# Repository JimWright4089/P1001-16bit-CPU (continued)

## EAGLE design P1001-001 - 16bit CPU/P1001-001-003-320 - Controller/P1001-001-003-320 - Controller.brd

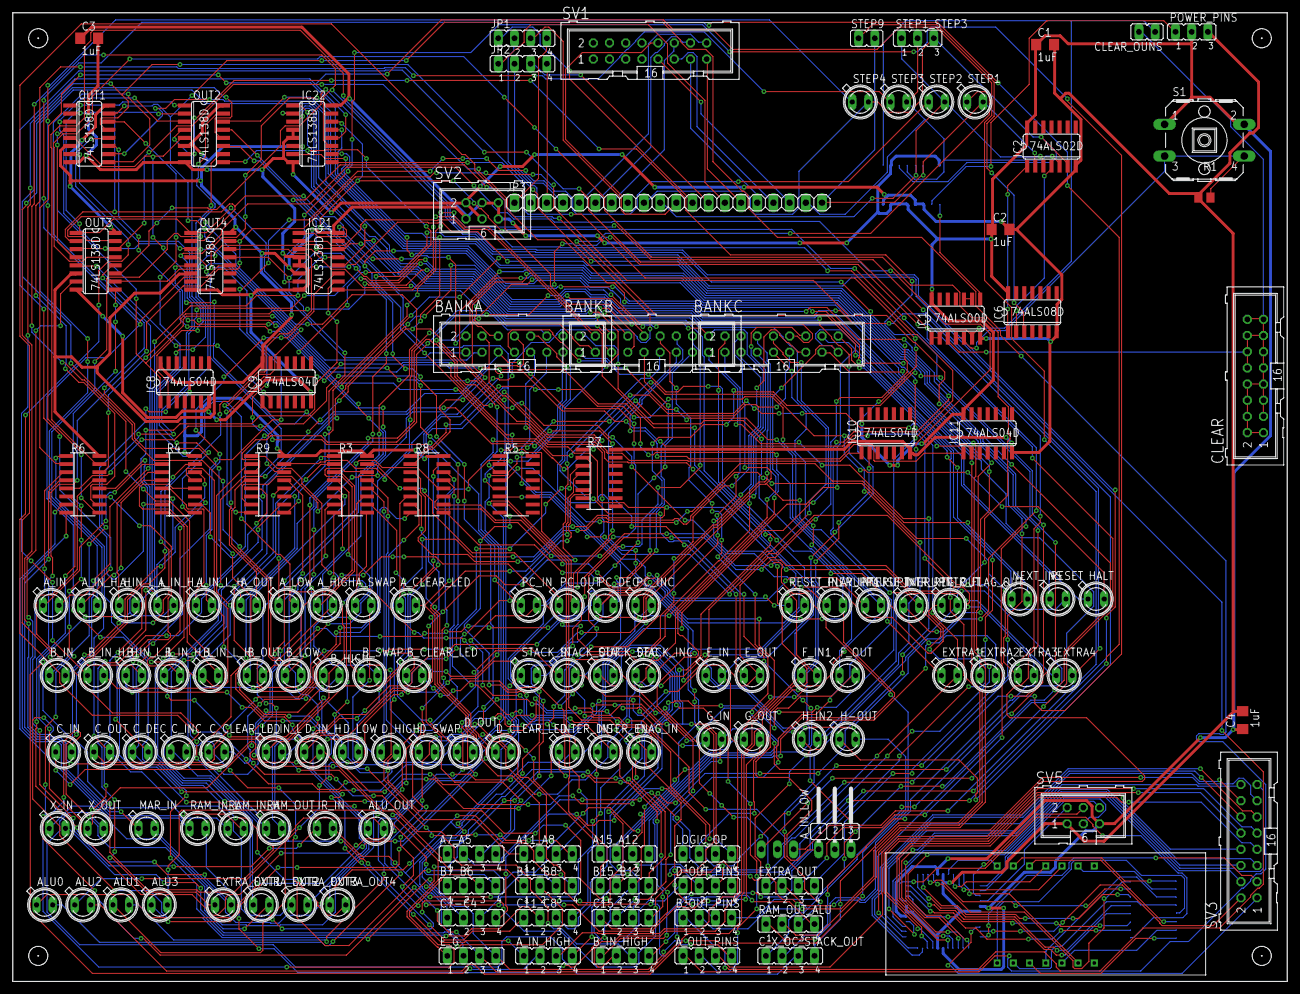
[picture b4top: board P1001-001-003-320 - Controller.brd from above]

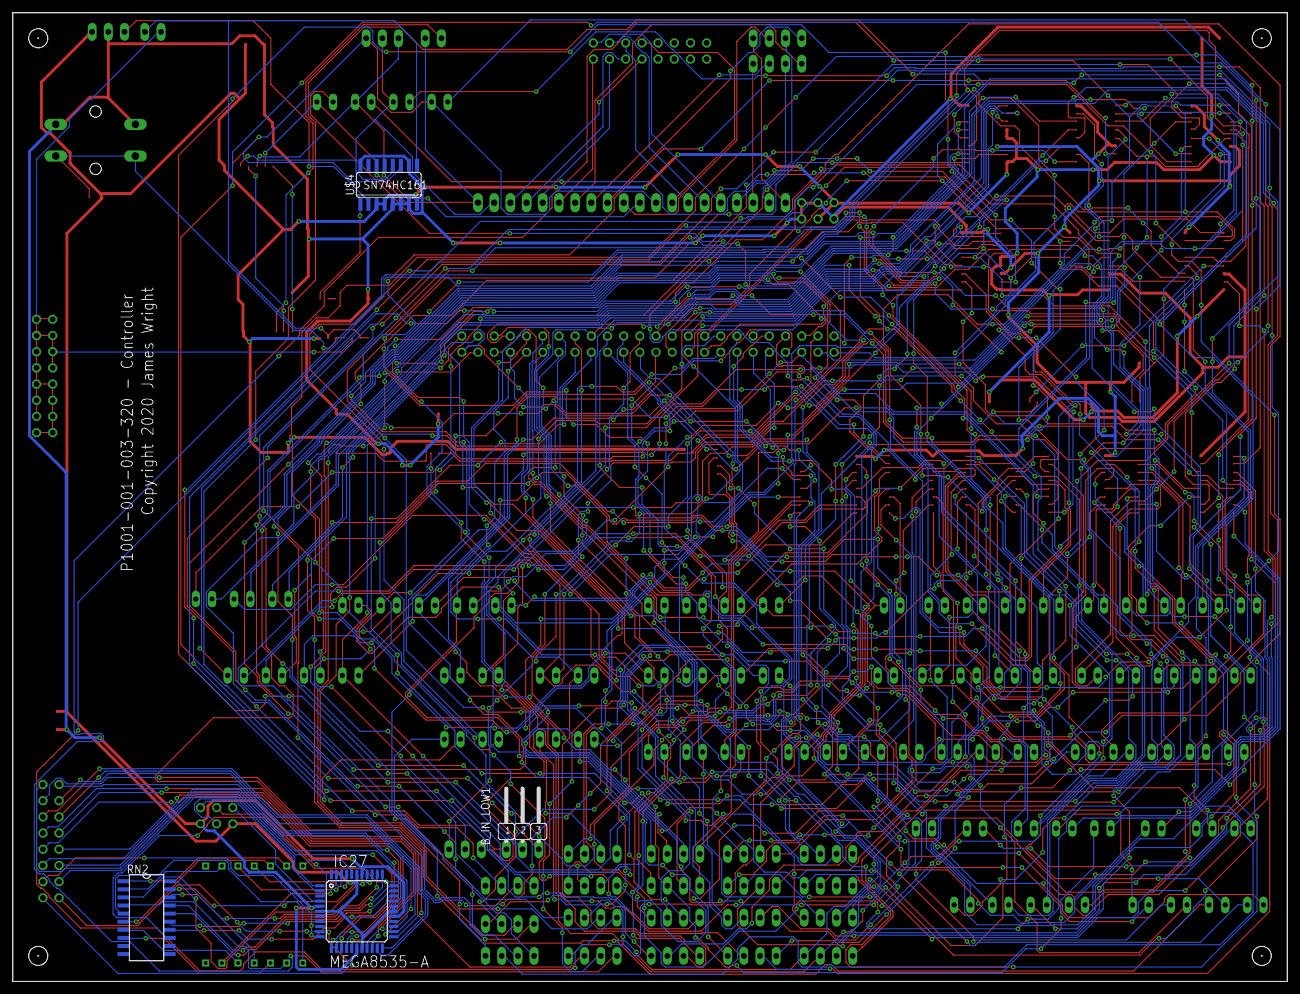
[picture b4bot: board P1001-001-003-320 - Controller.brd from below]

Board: 2 copper layers, 200.0 x 152.0 mm, 149 parts (4 on the bottom side), 248 nets.

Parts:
A7_A5, A11_A8, A15_A12: JP4
ALU0, ALU1, ALU2, ALU3: SFH482
ALU_OUT: SFH482
A_CLEAR_LED: SFH482
A_HIGH: SFH482
A_IN: SFH482
A_IN_HIGH: JP4
A_IN_H_H: SFH482
A_IN_H_L: SFH482
A_IN_LOW: JP2W
A_IN_L_H: SFH482
A_IN_L_L: SFH482
A_LOW: SFH482
A_OUT: SFH482
A_OUT_PINS: JP4
A_SWAP: SFH482
B7_B6, B11_B8, B15_B12: JP4
BANKA: ML16
BANKB: ML16
BANKC: ML16
B_CLEAR_LED: SFH482
B_HIGH: SFH482
B_IN: SFH482
B_IN_HIGH: JP4
B_IN_H_H: SFH482
B_IN_H_L: SFH482
B_IN_LOW1: JP2W
B_IN_L_H: SFH482
B_IN_L_L: SFH482
B_LOW: SFH482
B_OUT: SFH482
B_OUT_PINS: JP4
B_SWAP: SFH482
C1, C2, C3, C4: 1uF; C1206
C7-C4, C11_C8, C15_C12: JP4
CLEAR: ML16
CLEAR_OUNS: JP1
C_CLEAR_LED: SFH482
C_DEC: SFH482
C_IN: SFH482
C_INC: SFH482
C_OUT: SFH482
C_X_OC_STACK_OUT: JP4
D_CLEAR_LED: SFH482
D_HIGH: SFH482
D_IN_H: SFH482
D_IN_L: SFH482
D_LOW: SFH482
D_OUT: SFH482
D_OUT_PINS: JP4
D_SWAP: SFH482
EXTRA1, EXTRA2, EXTRA3, EXTRA4: SFH482
EXTRA_OUT: JP4
EXTRA_OUT1, EXTRA_OUT2, EXTRA_OUT3, EXTRA_OUT4: SFH482
E_G: JP4
E_IN: SFH482
E_OUT: SFH482
FLAG_IN: SFH482
F_IN1: SFH482
F_OUT: SFH482
G_IN: SFH482
G_OUT: SFH482
H-OUT: SFH482
HALT: SFH482
H_IN2: SFH482
IC1: 74ALS00D; SO14
IC2: 74ALS02D; SO14
IC6: 74ALS08D; SO14
IC8, IC9, IC10, IC11: 74ALS04D; SO14
IC21, IC22: 74LS138D; SO16
IC27: MEGA8535-A; TQFP44
INTER_DIS: SFH482
INTER_EN: SFH482
INTR_FLAG_OUT: SFH482
INTR_REG_OUT: SFH482
IR_IN: SFH482
JP1, JP2: JP4
JP3: 1X20
LOGIC_OP: JP4
MAR_IN: SFH482
NEXT_INS: SFH482
OUT1, OUT2, OUT3, OUT4: 74LS138D; SO16
PAUSE_INERUPT: SFH482
PC_DEC: SFH482
PC_IN: SFH482
PC_INC: SFH482
PC_OUT: SFH482
PLAY_INTERUPT: SFH482
POWER_PINS: JP2
R1: M0805
R3, R4, R5, R6, R7, R8, R9: SO16
RAM_IN_H: SFH482
RAM_IN_L: SFH482
RAM_OUT: SFH482
RAM_OUT_ALU: JP4
RESET: SFH482
RESET_INERUPT1: SFH482
RN2: SOMC20
S1: B3F-40XX
STACK_DEC: SFH482
STACK_IN: SFH482
STACK_INC: SFH482
STACK_OUT: SFH482
STEP1, STEP2, STEP3, STEP4: SFH482
STEP1_STEP3: JP2
STEP9: JP1
SV1, SV3: ML16
SV2, SV5: ML6
U$1: 4-DIGIT-7-SEGMENT
U$4: SN74HC161; SO16
X_IN: SFH482
X_OUT: SFH482

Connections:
!CLEAR: CLEAR_OUNS.1, IC1.1, IC1.2, IC1.6, U$4.9
A: IC27.37, RN2.20
B: IC27.36, RN2.19
C: IC27.35, RN2.18
CLEAR: CLEAR.1, CLEAR.2, CLEAR.3, CLEAR.4, CLEAR.5, CLEAR.6, CLEAR.7, CLEAR.8, CLEAR.9, CLEAR.10, CLEAR.11, CLEAR.12, CLEAR.13, CLEAR.14, CLEAR.15, CLEAR.16, CLEAR_OUNS.2, IC1.3
CLK: POWER_PINS.1, U$4.2
D: IC27.34, RN2.17
DATAA0: BANKA.1, OUT1.1, OUT2.1, OUT3.1, OUT4.1
DATAA1: BANKA.2, OUT1.2, OUT2.2, OUT3.2, OUT4.2
DATAA2: BANKA.3, OUT1.3, OUT2.3, OUT3.3, OUT4.3
DATAA3: BANKA.4, IC8.1, IC10.1, OUT1.4, OUT3.4
DATAA4: BANKA.5, IC9.1, IC11.1, OUT1.5, OUT2.5
DATAA5: A7_A5.2, BANKA.6, EXTRA1.K
DATAA6: A7_A5.3, BANKA.7, EXTRA2.K
DATAA7: A7_A5.4, BANKA.8, EXTRA3.K
DATAA8: A11_A8.1, BANKA.9, EXTRA4.A
DATAA9: A11_A8.2, A_CLEAR_LED.K, BANKA.10
DATAA10: A11_A8.3, BANKA.11, B_CLEAR_LED.K
DATAA11: A11_A8.4, BANKA.12, C_CLEAR_LED.K
DATAA12: A15_A12.1, BANKA.13, D_CLEAR_LED.K
DATAA13: A15_A12.2, BANKA.14, RESET_INERUPT1.K
DATAA14: A15_A12.3, BANKA.15, PAUSE_INERUPT.K
DATAA15: A15_A12.4, BANKA.16, PLAY_INTERUPT.K
DATAB0: BANKB.1, IC21.1
DATAB1: BANKB.2, IC21.2
DATAB2: BANKB.3, IC21.3
DATAB3: BANKB.4, IC22.1
DATAB4: BANKB.5, IC22.2
DATAB5: BANKB.6, IC22.3
DATAB6: B7_B6.3, BANKB.7, C_IN.K
DATAB7: B7_B6.4, BANKB.8, D_IN_L.K
DATAB8: B11_B8.1, BANKB.9, D_IN_H.K
DATAB9: B11_B8.2, BANKB.10, X_IN.K
DATAB10: B11_B8.3, BANKB.11, IR_IN.K
DATAB11: B11_B8.4, BANKB.12, MAR_IN.K
DATAB12: B15_B12.1, BANKB.13, PC_IN.K
DATAB13: B15_B12.2, BANKB.14, STACK_IN.K
DATAB14: B15_B12.3, BANKB.15, RAM_IN_L.K
DATAB15: B15_B12.4, BANKB.16, RAM_IN_H.K
DATAC0: ALU0.K, BANKC.1, LOGIC_OP.4
DATAC1: ALU1.K, BANKC.2, LOGIC_OP.3
DATAC2: ALU2.K, BANKC.3, LOGIC_OP.2
DATAC3: ALU3.K, BANKC.4, LOGIC_OP.1
DATAC4: BANKC.5, C7-C4.1, PC_DEC.A
DATAC5: BANKC.6, C7-C4.2, PC_INC.A
DATAC6: BANKC.7, C7-C4.3, STACK_INC.A
DATAC7: BANKC.8, C7-C4.4, STACK_DEC.A
DATAC8: BANKC.9, C11_C8.1, C_INC.A
DATAC9: BANKC.10, C11_C8.2, C_DEC.A
DATAC10: BANKC.11, C11_C8.3, FLAG_IN.A
DATAC11: BANKC.12, C11_C8.4, INTER_EN.A
DATAC12: BANKC.13, C15_C12.1, INTER_DIS.A
DATAC13: BANKC.14, C15_C12.2, RESET.A
DATAC14: BANKC.15, C15_C12.3, HALT.A
DATAC15: BANKC.16, C15_C12.4, NEXT_INS.A
DIG0: IC27.40, U$1.PIN14
DIG1: IC27.41, U$1.PIN11
DIG2: IC27.42, U$1.PIN10
DIG3: IC27.43, U$1.PIN6
DP: IC27.30, RN2.13
E: IC27.33, RN2.16
EXTERN_BUS0: IC27.9, SV3.1
EXTERN_BUS1: IC27.10, SV3.2
EXTERN_BUS2: IC27.11, SV3.3
EXTERN_BUS3: IC27.12, SV3.4
EXTERN_BUS4: IC27.13, SV3.5
EXTERN_BUS5: IC27.14, SV3.6
EXTERN_BUS6: IC27.15, SV3.7
EXTERN_BUS7: IC27.16, SV3.8
EXTERN_BUS8: IC27.19, SV3.9
EXTERN_BUS9: IC27.20, SV3.10
EXTERN_BUS10: IC27.21, SV3.11
EXTERN_BUS11: IC27.22, SV3.12
EXTERN_BUS12: IC27.23, SV3.13
EXTERN_BUS13: IC27.24, SV3.14
EXTERN_BUS14: IC27.25, SV3.15
EXTERN_BUS15: IC27.26, SV3.16
F: IC27.32, RN2.15
FIRST_STEP: IC6.3, STEP9.1
G: IC27.31, RN2.14
GND: C1.2, C2.2, C3.2, C4.2, IC1.7, IC2.7, IC6.7, IC8.7, IC9.7, IC10.7, IC11.7, IC21.4, IC21.5, IC21.8, IC22.4, IC22.5, IC22.8, IC27.6, IC27.18, IC27.28, IC27.29, IC27.39, OUT1.8, OUT2.8, OUT3.8, OUT4.8, POWER_PINS.3, R1.1, R7.16, SV2.2, SV2.3, SV5.1, U$4.3, U$4.4, U$4.8
IN_BUS0: IC2.2, JP3.20, STEP1.K, STEP9.2, U$4.14
IN_BUS1: IC2.3, JP3.10, STEP1_STEP3.1, STEP2.K, U$4.13
IN_BUS2: IC2.5, JP3.19, STEP1_STEP3.2, STEP3.K, U$4.12
IN_BUS3: IC2.6, JP3.9, STEP1_STEP3.3, STEP4.K, U$4.11
IN_BUS4: JP3.18, SV1.9
IN_BUS5: JP3.8, SV1.10
IN_BUS6: JP3.17, SV1.11
IN_BUS7: JP3.7, SV1.12
IN_BUS8: JP3.16, SV1.13
IN_BUS9: JP3.6, SV1.14
IN_BUS10: JP3.15, SV1.15
IN_BUS11: JP3.5, SV1.16
IN_BUS12: JP2.1, JP3.14
IN_BUS13: JP2.2, JP3.4
IN_BUS14: JP2.3, JP3.13
IN_BUS15: JP2.4, JP3.3
IN_BUS16: JP1.1, JP3.12
IN_BUS17: JP1.2, JP3.2
IN_BUS18: JP1.3, JP3.11
IN_BUS19: JP1.4, JP3.1
unnamed: IC1.4, IC1.5, R1.2, S1.3, S1.4
unnamed: EXTRA1.A, R8.1
unnamed: EXTRA2.A, R8.2
unnamed: R8.13, X_IN.A
unnamed: EXTRA4.K, R5.3
unnamed: EXTRA3.A, R8.3
unnamed: A_CLEAR_LED.A, R8.6
unnamed: C_CLEAR_LED.A, R8.8
unnamed: B_CLEAR_LED.A, R8.7
unnamed: R8.9, RESET_INERUPT1.A
unnamed: PAUSE_INERUPT.A, R8.10
unnamed: PLAY_INTERUPT.A, R8.11
unnamed: C_IN.A, R8.12
unnamed: D_IN_L.A, R8.15
unnamed: D_IN_H.A, R8.14
unnamed: PC_DEC.K, R6.2
unnamed: PC_INC.K, R6.1
unnamed: R6.8, RAM_IN_H.A
unnamed: R6.7, RAM_IN_L.A
unnamed: R6.6, STACK_IN.A
unnamed: PC_IN.A, R6.5
unnamed: MAR_IN.A, R6.4
unnamed: IR_IN.A, R6.3
unnamed: INTER_DIS.K, R5.7
unnamed: R6.15, STACK_INC.K
unnamed: R6.14, STACK_DEC.K
unnamed: C_INC.K, R6.13
unnamed: C_DEC.K, R6.12
unnamed: INTER_EN.K, R5.8
unnamed: FLAG_IN.K, R6.11
unnamed: A_IN.K, A_IN_LOW.1, IC21.14
unnamed: A_IN_LOW.2, A_IN_L_L.K, IC21.13
unnamed: A_IN_H_H.K, A_IN_LOW.3, IC21.12
unnamed: A_IN_HIGH.1, A_IN_L_H.K, IC21.11
unnamed: A_IN_HIGH.2, A_IN_H_L.K, IC21.10
unnamed: A_IN_HIGH.3, E_IN.K, IC21.9
unnamed: A_IN_HIGH.4, G_IN.K, IC21.7
unnamed: G_IN.A, R4.8
unnamed: E_IN.A, R4.7
unnamed: A_IN_H_L.A, R4.6
unnamed: D_CLEAR_LED.A, R8.5
unnamed: IC1.8, U$4.1
unnamed: B_IN_HIGH.1, H_IN2.A, IC22.7
unnamed: B_IN_HIGH.2, F_IN1.A, IC22.9
unnamed: B_IN_HIGH.3, B_IN_H_L.A, IC22.10
unnamed: B_IN_HIGH.4, B_IN_L_H.A, IC22.11
unnamed: B_IN_H_H.A, B_IN_LOW1.1, IC22.12
unnamed: B_IN_LOW1.2, B_IN_L_L.A, IC22.13
unnamed: A_OUT.K, A_OUT_PINS.1, OUT1.15
unnamed: B_IN.A, B_IN_LOW1.3, IC22.14
unnamed: H_IN2.K, R4.9
unnamed: F_IN1.K, R4.10
unnamed: B_IN_H_L.K, R4.11
unnamed: R9.14, STEP2.A
unnamed: A_LOW.K, A_OUT_PINS.2, OUT1.14
unnamed: A_HIGH.K, A_OUT_PINS.3, OUT1.13
unnamed: A_OUT_PINS.4, A_SWAP.K, OUT1.12
unnamed: R5.6, RESET.K
unnamed: HALT.K, R5.5
unnamed: IC2.4, IC6.2
unnamed: IC2.1, IC6.1
unnamed: NEXT_INS.K, R5.4
unnamed: A_IN_L_H.A, R4.5
unnamed: A_IN_H_H.A, R4.4
unnamed: A_IN_L_L.A, R4.3
unnamed: ALU0.A, R7.4
unnamed: ALU1.A, R7.3
unnamed: ALU2.A, R7.1
unnamed: ALU3.A, R7.2
unnamed: A_IN.A, R4.2
unnamed: B_IN_L_H.K, R4.12
unnamed: B_IN_H_H.K, R4.13
unnamed: B_OUT.K, B_OUT_PINS.1, OUT1.11
unnamed: B_LOW.K, B_OUT_PINS.2, OUT1.10
unnamed: B_HIGH.K, B_OUT_PINS.3, OUT1.9
unnamed: B_OUT_PINS.4, B_SWAP.K, OUT1.7
unnamed: C_OUT.K, D_OUT_PINS.4, OUT2.15
unnamed: D_OUT.K, D_OUT_PINS.3, OUT2.14
unnamed: D_LOW.K, D_OUT_PINS.2, OUT2.13
unnamed: D_HIGH.K, D_OUT_PINS.1, OUT2.12
unnamed: C_X_OC_STACK_OUT.4, D_SWAP.K, OUT2.11
unnamed: C_X_OC_STACK_OUT.3, OUT2.10, X_OUT.K
unnamed: C_X_OC_STACK_OUT.2, OUT2.9, PC_OUT.K
unnamed: C_X_OC_STACK_OUT.1, OUT2.7, STACK_OUT.K
unnamed: C_OUT.A, R3.9
unnamed: D_OUT.A, R3.10
unnamed: B_SWAP.A, R3.8
unnamed: B_HIGH.A, R3.7
unnamed: B_LOW.A, R3.6
unnamed: B_OUT.A, R3.5
unnamed: A_SWAP.A, R3.4
unnamed: A_HIGH.A, R3.3
unnamed: A_LOW.A, R3.2
unnamed: A_OUT.A, R3.1
unnamed: D_LOW.A, R3.11
unnamed: D_HIGH.A, R3.12
unnamed: PC_OUT.A, R3.15
unnamed: D_SWAP.A, R3.13
unnamed: R3.14, X_OUT.A
unnamed: OUT3.15, RAM_OUT.K, RAM_OUT_ALU.1
unnamed: INTR_REG_OUT.K, OUT3.14, RAM_OUT_ALU.2
unnamed: INTR_FLAG_OUT.K, OUT3.13, RAM_OUT_ALU.3
unnamed: ALU_OUT.K, OUT3.12, RAM_OUT_ALU.4
unnamed: E_G.1, E_OUT.K, OUT3.11
unnamed: E_G.2, F_OUT.K, OUT3.10
unnamed: E_G.3, G_OUT.K, OUT3.9
unnamed: E_G.4, H-OUT.K, OUT3.7
unnamed: R9.1, STACK_OUT.A
unnamed: R9.2, RAM_OUT.A
unnamed: G_OUT.A, R9.8
unnamed: H-OUT.A, R9.9
unnamed: EXTRA_OUT1.A, R9.10
unnamed: EXTRA_OUT2.A, R9.11
unnamed: INTR_REG_OUT.A, R9.3
unnamed: INTR_FLAG_OUT.A, R9.4
unnamed: ALU_OUT.A, R9.5
unnamed: IC27.1, SV5.3
unnamed: IC27.3, SV5.4
unnamed: IC27.2, SV5.6
unnamed: IC27.4, SV5.2
unnamed: RN2.1, U$1.PIN13
unnamed: RN2.2, U$1.PIN9
unnamed: RN2.3, U$1.PIN4
unnamed: RN2.4, U$1.PIN2
unnamed: RN2.5, U$1.PIN1
unnamed: RN2.6, U$1.PIN12
unnamed: RN2.7, U$1.PIN5
unnamed: RN2.8, U$1.PIN3
unnamed: R9.15, STEP1.A
unnamed: B_IN_L_L.K, R4.14
unnamed: R6.10, STEP3.A
unnamed: R6.9, STEP4.A
unnamed: B_IN.K, R4.15
unnamed: E_OUT.A, R9.6
unnamed: F_OUT.A, R9.7
unnamed: EXTRA_OUT3.A, R9.12
unnamed: EXTRA_OUT4.A, R9.13
unnamed: EXTRA_OUT.4, EXTRA_OUT1.K, OUT4.15
unnamed: EXTRA_OUT.3, EXTRA_OUT2.K, OUT4.14
unnamed: EXTRA_OUT.2, EXTRA_OUT3.K, OUT4.13
unnamed: EXTRA_OUT.1, EXTRA_OUT4.K, OUT4.12
unnamed: IC8.2, OUT2.4
unnamed: IC9.2, OUT3.5
unnamed: IC10.2, OUT4.4
unnamed: IC11.2, OUT4.5
NEXT_INS: IC1.9, IC1.10
VCC: C1.1, C2.1, C3.1, C4.1, IC1.14, IC2.14, IC6.14, IC8.14, IC9.14, IC10.14, IC11.14, IC21.6, IC21.16, IC22.6, IC22.16, IC27.5, IC27.17, IC27.27, IC27.38, OUT1.6, OUT1.16, OUT2.6, OUT2.16, OUT3.6, OUT3.16, OUT4.6, OUT4.16, POWER_PINS.2, R3.16, R4.16, R6.16, R8.16, R9.16, S1.1, S1.2, SV2.1, SV2.4, SV2.5, SV2.6, SV5.5, U$4.5, U$4.6, U$4.7, U$4.10, U$4.16

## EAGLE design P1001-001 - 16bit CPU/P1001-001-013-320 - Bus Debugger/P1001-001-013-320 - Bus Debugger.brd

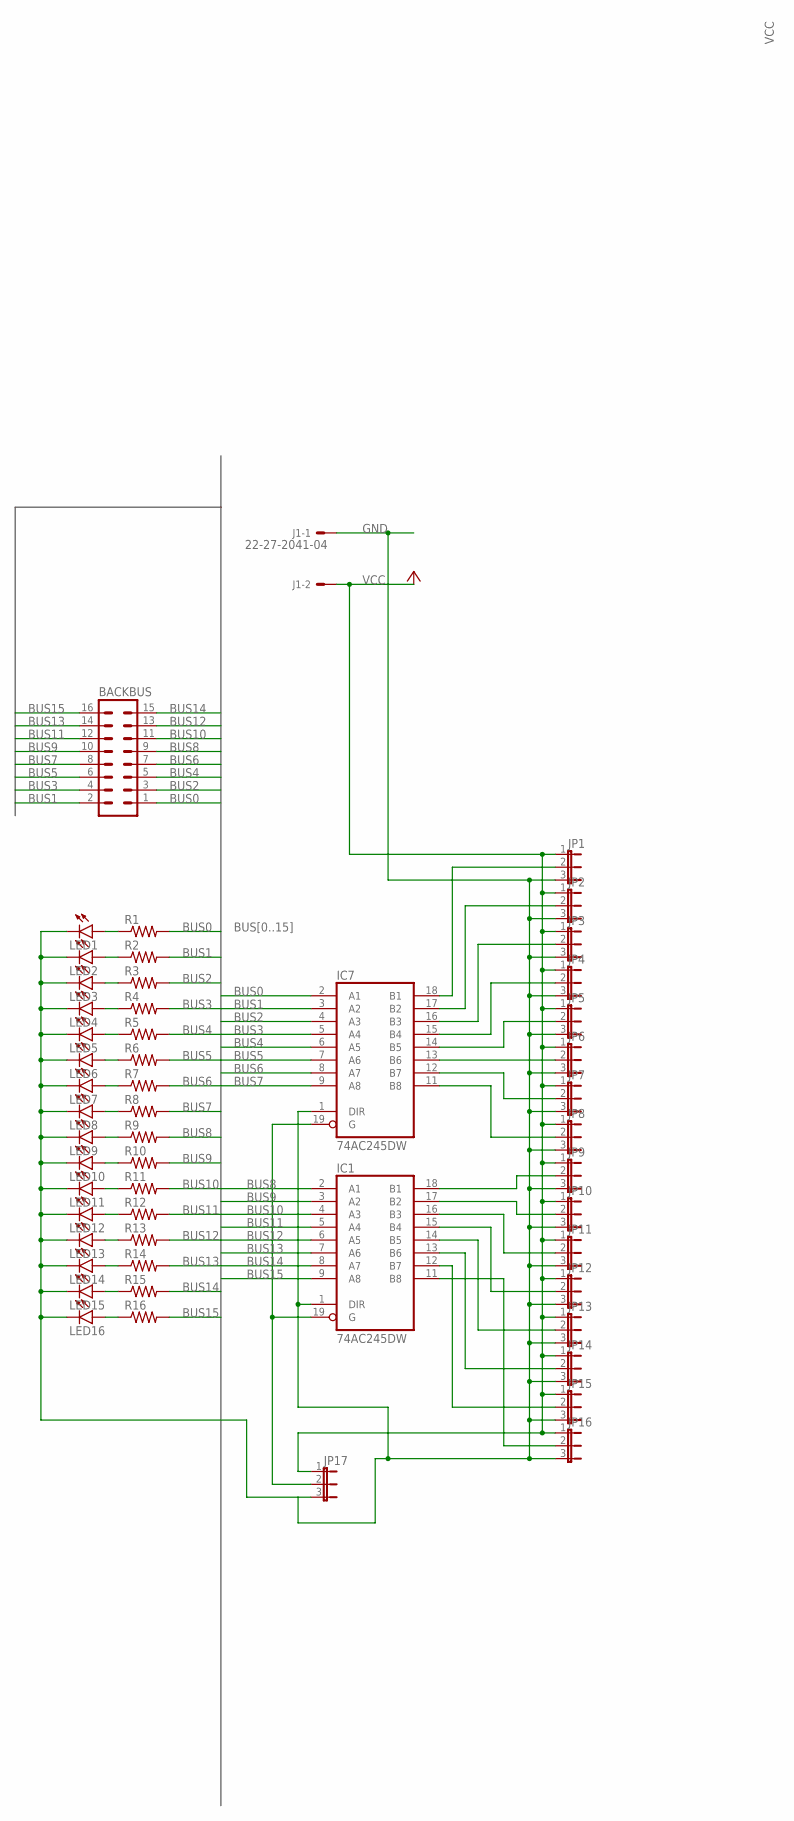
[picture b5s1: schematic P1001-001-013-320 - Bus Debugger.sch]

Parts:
BACKBUS: ML16
IC1, IC7: 74AC245DW; SO20W
J1: 22-27-2041-04; 6410-04
JP1, JP2, JP3, JP4, JP5, JP6, JP7, JP8, JP9, JP10, JP11, JP12, JP13, JP14, JP15, JP16, JP17: JP2E; JP2
LED1, LED2, LED3, LED4, LED5, LED6, LED7, LED8, LED9, LED10, LED11, LED12, LED13, LED14, LED15, LED16: LED5MM
R1, R2, R3, R4, R5, R6, R7, R8, R9, R10, R11, R12, R13, R14, R15, R16: R-US_0204/2V; 0204V

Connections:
BUS0: BACKBUS.1, IC7.2 (A1), R1.2
BUS1: BACKBUS.2, IC7.3 (A2), R2.2
BUS2: BACKBUS.3, IC7.4 (A3), R3.2
BUS3: BACKBUS.4, IC7.5 (A4), R4.2
BUS4: BACKBUS.5, IC7.6 (A5), R5.2
BUS5: BACKBUS.6, IC7.7 (A6), R6.2
BUS6: BACKBUS.7, IC7.8 (A7), R7.2
BUS7: BACKBUS.8, IC7.9 (A8), R8.2
BUS8: BACKBUS.9, IC1.2 (A1), R9.2
BUS9: BACKBUS.10, IC1.3 (A2), R10.2
BUS10: BACKBUS.11, IC1.4 (A3), R11.2
BUS11: BACKBUS.12, IC1.5 (A4), R12.2
BUS12: BACKBUS.13, IC1.6 (A5), R13.2
BUS13: BACKBUS.14, IC1.7 (A6), R14.2
BUS14: BACKBUS.15, IC1.8 (A7), R15.2
BUS15: BACKBUS.16, IC1.9 (A8), R16.2
GND: IC1.1 (DIR), IC1.10 (GND), IC7.1 (DIR), IC7.10 (GND), J1.1, JP1.3, JP2.3, JP3.3, JP4.3, JP5.3, JP6.3, JP7.3, JP8.3, JP9.3, JP10.3, JP11.3, JP12.3, JP13.3, JP14.3, JP15.3, JP16.3, JP17.3, LED1.K (C), LED2.K (C), LED3.K (C), LED4.K (C), LED5.K (C), LED6.K (C), LED7.K (C), LED8.K (C), LED9.K (C), LED10.K (C), LED11.K (C), LED12.K (C), LED13.K (C), LED14.K (C), LED15.K (C), LED16.K (C)
unnamed: IC7.18 (B1), JP1.2
unnamed: IC7.17 (B2), JP2.2
unnamed: IC7.16 (B3), JP3.2
unnamed: IC7.15 (B4), JP4.2
unnamed: IC7.14 (B5), JP5.2
unnamed: IC7.13 (B6), JP6.2
unnamed: IC7.12 (B7), JP7.2
unnamed: IC7.11 (B8), JP8.2
unnamed: IC1.18 (B1), JP9.2
unnamed: IC1.17 (B2), JP10.2
unnamed: IC1.16 (B3), JP11.2
unnamed: IC1.15 (B4), JP12.2
unnamed: IC1.14 (B5), JP13.2
unnamed: IC1.13 (B6), JP14.2
unnamed: IC1.12 (B7), JP15.2
unnamed: IC1.11 (B8), JP16.2
unnamed: IC1.19 (G), IC7.19 (G), JP17.2
unnamed: LED13.A, R13.1
unnamed: LED14.A, R14.1
unnamed: LED15.A, R15.1
unnamed: LED16.A, R16.1
unnamed: LED8.A, R8.1
unnamed: LED7.A, R7.1
unnamed: LED6.A, R6.1
unnamed: LED5.A, R5.1
unnamed: LED4.A, R4.1
unnamed: LED3.A, R3.1
unnamed: LED2.A, R2.1
unnamed: LED1.A, R1.1
unnamed: LED9.A, R9.1
unnamed: LED10.A, R10.1
unnamed: LED11.A, R11.1
unnamed: LED12.A, R12.1
VCC: IC1.20 (VCC), IC7.20 (VCC), J1.2, JP1.1, JP2.1, JP3.1, JP4.1, JP5.1, JP6.1, JP7.1, JP8.1, JP9.1, JP10.1, JP11.1, JP12.1, JP13.1, JP14.1, JP15.1, JP16.1, JP17.1

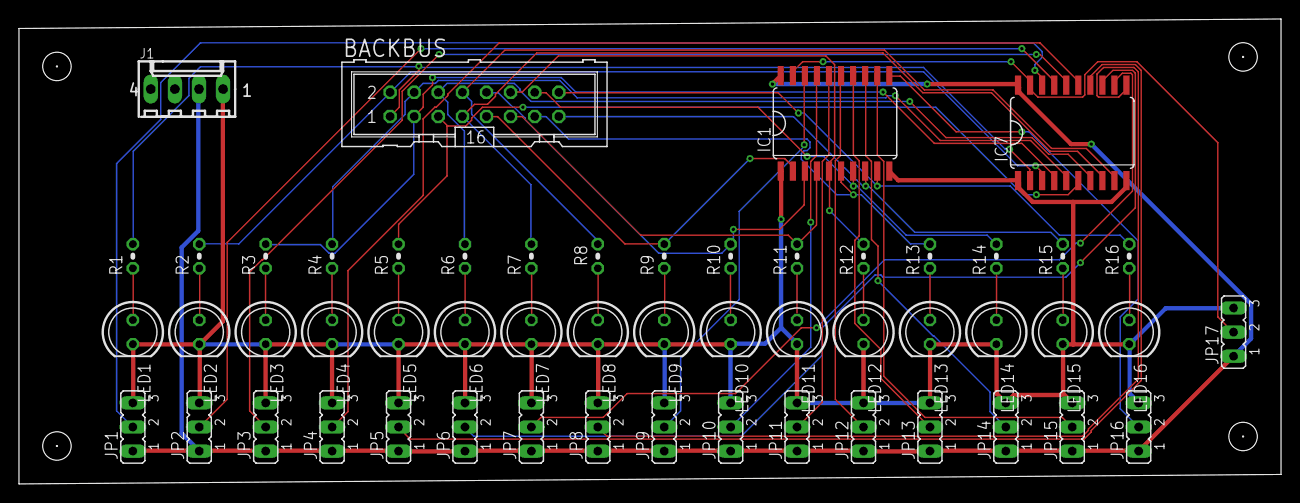
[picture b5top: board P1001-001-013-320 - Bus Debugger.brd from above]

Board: 2 copper layers, 133.0 x 49.0 mm, 53 parts (0 on the bottom side), 51 nets.

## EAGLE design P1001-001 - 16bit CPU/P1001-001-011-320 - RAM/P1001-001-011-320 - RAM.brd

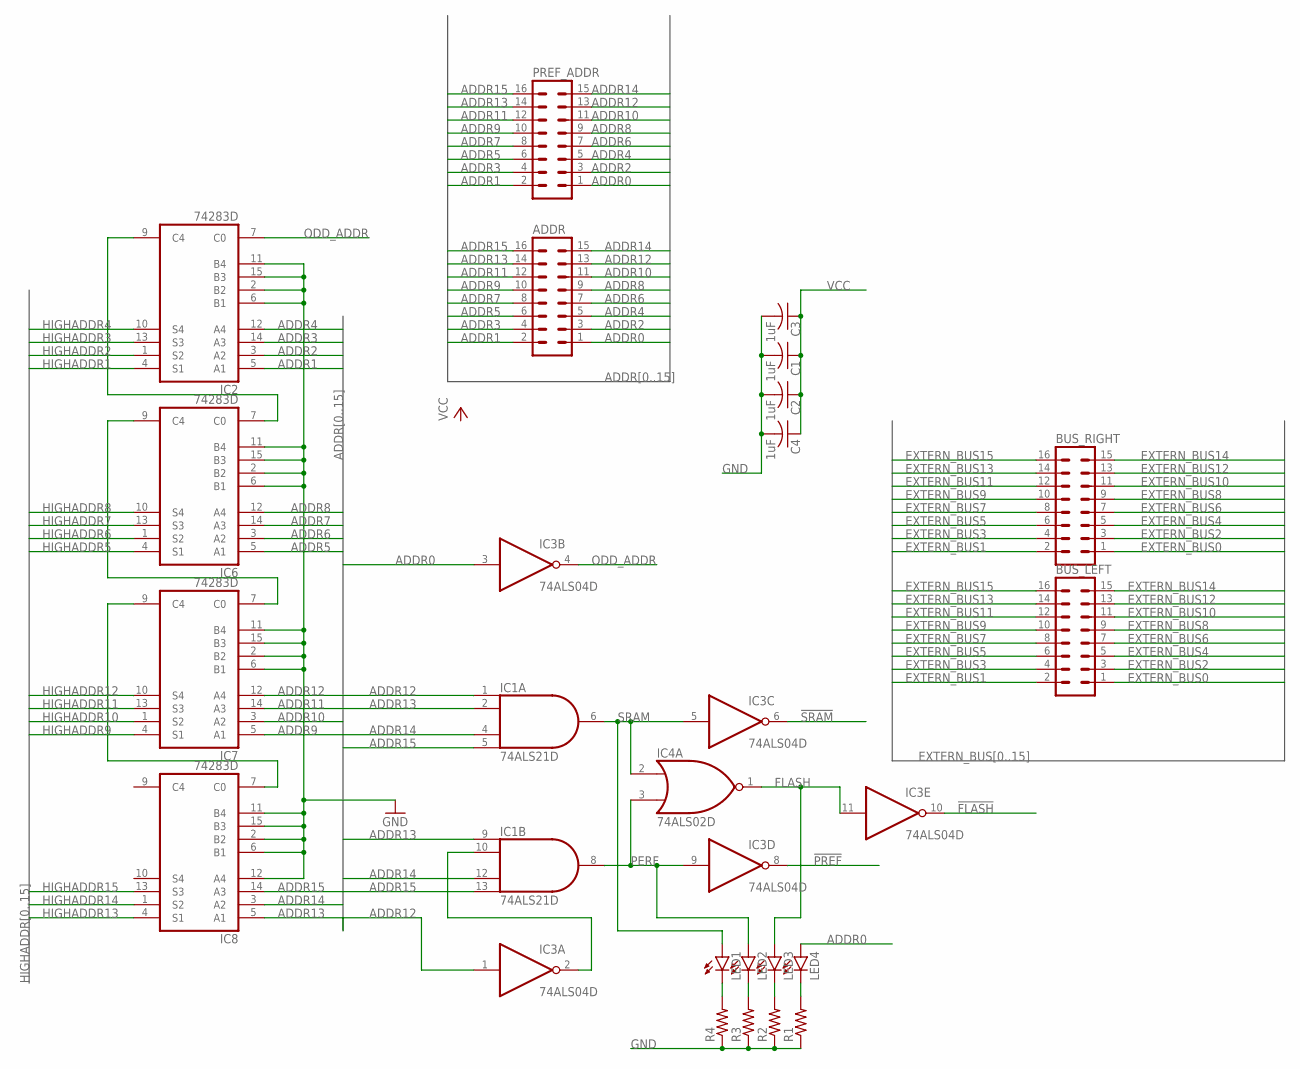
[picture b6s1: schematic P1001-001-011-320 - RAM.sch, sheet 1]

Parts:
ADDR: ML16
BUS_LEFT: ML16
BUS_RIGHT: ML16
C1, C2, C3, C4: 1uF; C1206
IC1: 74ALS21D; SO14
IC2, IC6, IC7, IC8: 74283D; SO16
IC3: 74ALS04D; SO14
IC4: 74ALS02D; SO14
LED1, LED2, LED3, LED4: LED5MM
PREF_ADDR: ML16
R1, R2, R3, R4: R-US_M1206; M1206

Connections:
!FLASH: IC3.10 (O); also elsewhere on the board
!PREF: IC3.8 (O); also elsewhere on the board
!SRAM: IC3.6 (O); also elsewhere on the board
ADDR0: ADDR.1, IC3.3 (I), LED4.A, PREF_ADDR.1; also elsewhere on the board
ADDR1: ADDR.2, IC2.5 (A1), PREF_ADDR.2; also elsewhere on the board
ADDR2: ADDR.3, IC2.3 (A2), PREF_ADDR.3; also elsewhere on the board
ADDR3: ADDR.4, IC2.14 (A3), PREF_ADDR.4; also elsewhere on the board
ADDR4: ADDR.5, IC2.12 (A4), PREF_ADDR.5; also elsewhere on the board
ADDR5: ADDR.6, IC6.5 (A1), PREF_ADDR.6; also elsewhere on the board
ADDR6: ADDR.7, IC6.3 (A2), PREF_ADDR.7; also elsewhere on the board
ADDR7: ADDR.8, IC6.14 (A3), PREF_ADDR.8; also elsewhere on the board
ADDR8: ADDR.9, IC6.12 (A4), PREF_ADDR.9; also elsewhere on the board
ADDR9: ADDR.10, IC7.5 (A1), PREF_ADDR.10; also elsewhere on the board
ADDR10: ADDR.11, IC7.3 (A2), PREF_ADDR.11; also elsewhere on the board
ADDR11: ADDR.12, IC7.14 (A3), PREF_ADDR.12; also elsewhere on the board
ADDR12: ADDR.13, IC1.1 (I0), IC3.1 (I), IC7.12 (A4), PREF_ADDR.13; also elsewhere on the board
ADDR13: ADDR.14, IC1.2 (I1), IC1.9 (I0), IC8.5 (A1), PREF_ADDR.14; also elsewhere on the board
ADDR14: ADDR.15, IC1.4 (I2), IC1.12 (I2), IC8.3 (A2), PREF_ADDR.15; also elsewhere on the board
ADDR15: ADDR.16, IC1.5 (I3), IC1.13 (I3), IC8.14 (A3), PREF_ADDR.16; also elsewhere on the board
EXTERN_BUS0: BUS_LEFT.1, BUS_RIGHT.1; also elsewhere on the board
EXTERN_BUS1: BUS_LEFT.2, BUS_RIGHT.2; also elsewhere on the board
EXTERN_BUS2: BUS_LEFT.3, BUS_RIGHT.3; also elsewhere on the board
EXTERN_BUS3: BUS_LEFT.4, BUS_RIGHT.4; also elsewhere on the board
EXTERN_BUS4: BUS_LEFT.5, BUS_RIGHT.5; also elsewhere on the board
EXTERN_BUS5: BUS_LEFT.6, BUS_RIGHT.6; also elsewhere on the board
EXTERN_BUS6: BUS_LEFT.7, BUS_RIGHT.7; also elsewhere on the board
EXTERN_BUS7: BUS_LEFT.8, BUS_RIGHT.8; also elsewhere on the board
EXTERN_BUS8: BUS_LEFT.9, BUS_RIGHT.9; also elsewhere on the board
EXTERN_BUS9: BUS_LEFT.10, BUS_RIGHT.10; also elsewhere on the board
EXTERN_BUS10: BUS_LEFT.11, BUS_RIGHT.11; also elsewhere on the board
EXTERN_BUS11: BUS_LEFT.12, BUS_RIGHT.12; also elsewhere on the board
EXTERN_BUS12: BUS_LEFT.13, BUS_RIGHT.13; also elsewhere on the board
EXTERN_BUS13: BUS_LEFT.14, BUS_RIGHT.14; also elsewhere on the board
EXTERN_BUS14: BUS_LEFT.15, BUS_RIGHT.15; also elsewhere on the board
EXTERN_BUS15: BUS_LEFT.16, BUS_RIGHT.16; also elsewhere on the board
FLASH: IC3.11 (I), IC4.1 (O), LED3.A
GND: C1.2, C2.2, C3.2, C4.2, IC1.7 (GND), IC2.2 (B2), IC2.6 (B1), IC2.8 (GND), IC2.11 (B4), IC2.15 (B3), IC3.7 (GND), IC4.7 (GND), IC6.2 (B2), IC6.6 (B1), IC6.8 (GND), IC6.11 (B4), IC6.15 (B3), IC7.2 (B2), IC7.6 (B1), IC7.8 (GND), IC7.11 (B4), IC7.15 (B3), IC8.2 (B2), IC8.6 (B1), IC8.8 (GND), IC8.11 (B4), IC8.12 (A4), IC8.15 (B3), R1.1, R2.1, R3.1, R4.1; also elsewhere on the board
HIGHADDR1: IC2.4 (S1); also elsewhere on the board
HIGHADDR2: IC2.1 (S2); also elsewhere on the board
HIGHADDR3: IC2.13 (S3); also elsewhere on the board
HIGHADDR4: IC2.10 (S4); also elsewhere on the board
HIGHADDR5: IC6.4 (S1); also elsewhere on the board
HIGHADDR6: IC6.1 (S2); also elsewhere on the board
HIGHADDR7: IC6.13 (S3); also elsewhere on the board
HIGHADDR8: IC6.10 (S4); also elsewhere on the board
HIGHADDR9: IC7.4 (S1); also elsewhere on the board
HIGHADDR10: IC7.1 (S2); also elsewhere on the board
HIGHADDR11: IC7.13 (S3); also elsewhere on the board
HIGHADDR12: IC7.10 (S4); also elsewhere on the board
HIGHADDR13: IC8.4 (S1); also elsewhere on the board
HIGHADDR14: IC8.1 (S2); also elsewhere on the board
HIGHADDR15: IC8.13 (S3); also elsewhere on the board
unnamed: IC1.10 (I1), IC3.2 (O)
unnamed: LED1.K (C), R4.2
unnamed: LED2.K (C), R3.2
unnamed: LED3.K (C), R2.2
unnamed: LED4.K (C), R1.2
unnamed: IC2.9 (C4), IC6.7 (C0)
unnamed: IC6.9 (C4), IC7.7 (C0)
unnamed: IC7.9 (C4), IC8.7 (C0)
ODD_ADDR: IC2.7 (C0), IC3.4 (O); also elsewhere on the board
PERF: IC1.8 (O), IC3.9 (I), IC4.3 (I1), LED2.A
SRAM: IC1.6 (O), IC3.5 (I), IC4.2 (I0), LED1.A
VCC: C1.1, C2.1, C3.1, C4.1, IC1.14 (VCC), IC2.16 (VCC), IC3.14 (VCC), IC4.14 (VCC), IC6.16 (VCC), IC7.16 (VCC), IC8.16 (VCC); also elsewhere on the board

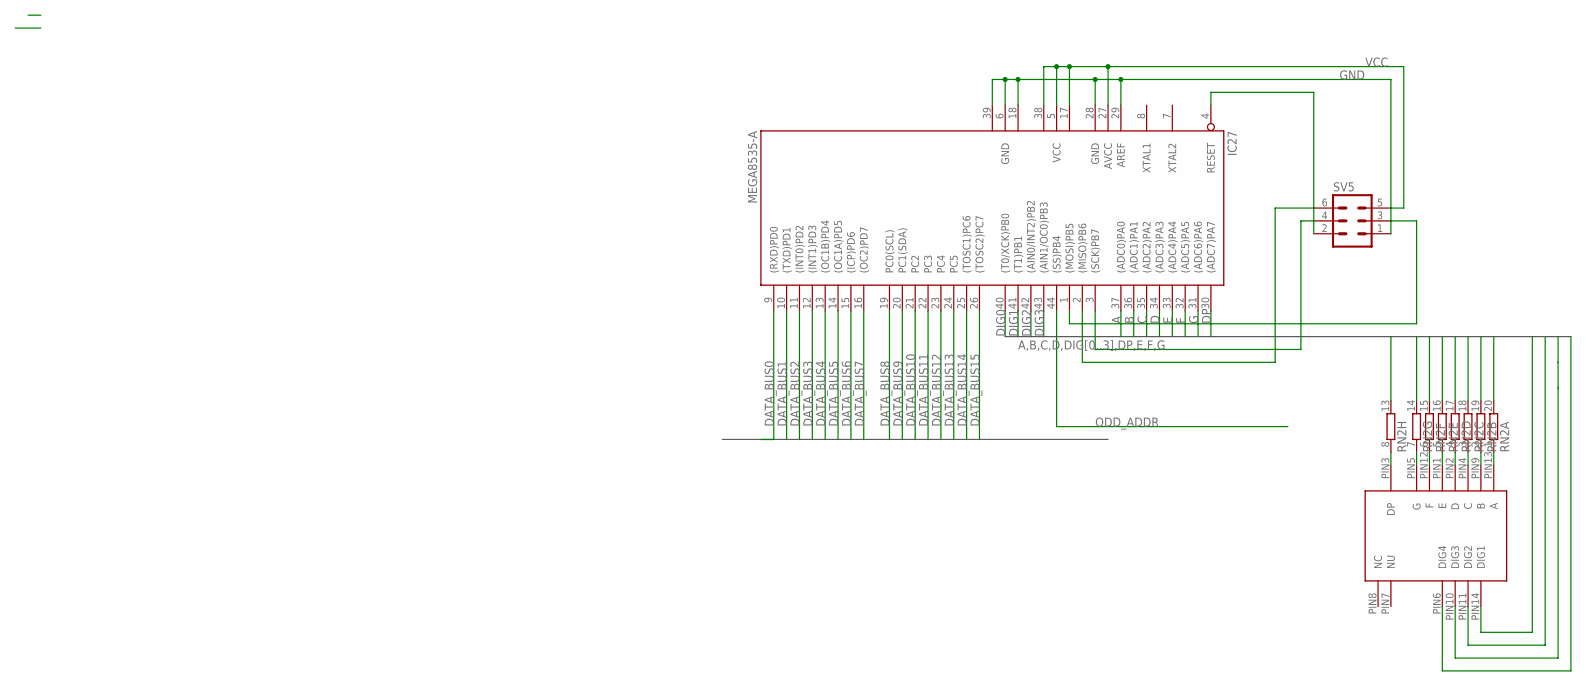
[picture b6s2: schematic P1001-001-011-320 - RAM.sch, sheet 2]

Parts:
IC27: MEGA8535-A; TQFP44
RN2: 10R-NSOMC; SOMC20
SV5: ML6
U$1: 4-DIGIT-7-SEGMENT

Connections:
A: IC27.37 ((ADC0)PA0), RN2.20 (2)
B: IC27.36 ((ADC1)PA1), RN2.19 (2)
C: IC27.35 ((ADC2)PA2), RN2.18 (2)
D: IC27.34 ((ADC3)PA3), RN2.17 (2)
DATA_BUS0: IC27.9 ((RXD)PD0); also elsewhere on the board
DATA_BUS1: IC27.10 ((TXD)PD1); also elsewhere on the board
DATA_BUS2: IC27.11 ((INT0)PD2); also elsewhere on the board
DATA_BUS3: IC27.12 ((INT1)PD3); also elsewhere on the board
DATA_BUS4: IC27.13 ((OC1B)PD4); also elsewhere on the board
DATA_BUS5: IC27.14 ((OC1A)PD5); also elsewhere on the board
DATA_BUS6: IC27.15 ((ICP)PD6); also elsewhere on the board
DATA_BUS7: IC27.16 ((OC2)PD7); also elsewhere on the board
DATA_BUS8: IC27.19 (PC0(SCL)); also elsewhere on the board
DATA_BUS9: IC27.20 (PC1(SDA)); also elsewhere on the board
DATA_BUS10: IC27.21 (PC2); also elsewhere on the board
DATA_BUS11: IC27.22 (PC3); also elsewhere on the board
DATA_BUS12: IC27.23 (PC4); also elsewhere on the board
DATA_BUS13: IC27.24 (PC5); also elsewhere on the board
DATA_BUS14: IC27.25 ((TOSC1)PC6); also elsewhere on the board
DATA_BUS15: IC27.26 ((TOSC2)PC7); also elsewhere on the board
DIG0: IC27.40 ((T0/XCK)PB0), U$1.PIN14 (DIG1)
DIG1: IC27.41 ((T1)PB1), U$1.PIN11 (DIG2)
DIG2: IC27.42 ((AIN0/INT2)PB2), U$1.PIN10 (DIG3)
DIG3: IC27.43 ((AIN1/OC0)PB3), U$1.PIN6 (DIG4)
DP: IC27.30 ((ADC7)PA7), RN2.13 (2)
E: IC27.33 ((ADC4)PA4), RN2.16 (2)
F: IC27.32 ((ADC5)PA5), RN2.15 (2)
G: IC27.31 ((ADC6)PA6), RN2.14 (2)
GND: IC27.6 (GND), IC27.18 (GND1), IC27.28 (GND), IC27.29 (AREF), IC27.39 (GND2), SV5.1; also elsewhere on the board
unnamed: IC27.1 ((MOSI)PB5), SV5.3
unnamed: IC27.3 ((SCK)PB7), SV5.4
unnamed: IC27.2 ((MISO)PB6), SV5.6
unnamed: IC27.4 (RESET), SV5.2
unnamed: RN2.1, U$1.PIN13 (A)
unnamed: RN2.2 (1), U$1.PIN9 (B)
unnamed: RN2.3 (1), U$1.PIN4 (C)
unnamed: RN2.4 (1), U$1.PIN2 (D)
unnamed: RN2.5 (1), U$1.PIN1 (E)
unnamed: RN2.6 (1), U$1.PIN12 (F)
unnamed: RN2.7 (1), U$1.PIN5 (G)
unnamed: RN2.8 (1), U$1.PIN3 (DP)
ODD_ADDR: IC27.44 ((SS)PB4); also elsewhere on the board
VCC: IC27.5 (VCC), IC27.17 (VCC1), IC27.27 (AVCC), IC27.38 (VCC2), SV5.5; also elsewhere on the board

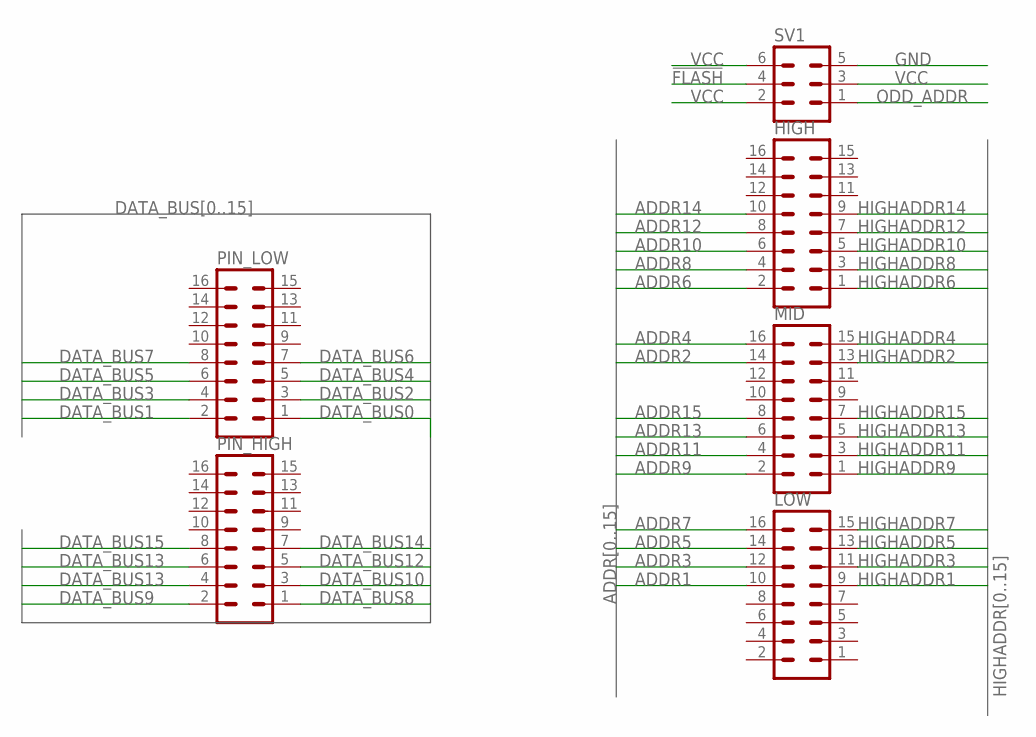
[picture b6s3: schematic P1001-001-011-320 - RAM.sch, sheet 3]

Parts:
HIGH: ML16
LOW: ML16
MID: ML16
PIN_HIGH: ML16
PIN_LOW: ML16
SV1: ML6

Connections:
!FLASH: SV1.4; also elsewhere on the board
ADDR1: LOW.10; also elsewhere on the board
ADDR2: MID.14; also elsewhere on the board
ADDR3: LOW.12; also elsewhere on the board
ADDR4: MID.16; also elsewhere on the board
ADDR5: LOW.14; also elsewhere on the board
ADDR6: HIGH.2; also elsewhere on the board
ADDR7: LOW.16; also elsewhere on the board
ADDR8: HIGH.4; also elsewhere on the board
ADDR9: MID.2; also elsewhere on the board
ADDR10: HIGH.6; also elsewhere on the board
ADDR11: MID.4; also elsewhere on the board
ADDR12: HIGH.8; also elsewhere on the board
ADDR13: MID.6; also elsewhere on the board
ADDR14: HIGH.10; also elsewhere on the board
ADDR15: MID.8; also elsewhere on the board
DATA_BUS0: PIN_LOW.1; also elsewhere on the board
DATA_BUS1: PIN_LOW.2; also elsewhere on the board
DATA_BUS2: PIN_LOW.3; also elsewhere on the board
DATA_BUS3: PIN_LOW.4; also elsewhere on the board
DATA_BUS4: PIN_LOW.5; also elsewhere on the board
DATA_BUS5: PIN_LOW.6; also elsewhere on the board
DATA_BUS6: PIN_LOW.7; also elsewhere on the board
DATA_BUS7: PIN_LOW.8; also elsewhere on the board
DATA_BUS8: PIN_HIGH.1; also elsewhere on the board
DATA_BUS9: PIN_HIGH.2; also elsewhere on the board
DATA_BUS10: PIN_HIGH.3; also elsewhere on the board
DATA_BUS11: PIN_HIGH.4; also elsewhere on the board
DATA_BUS12: PIN_HIGH.5; also elsewhere on the board
DATA_BUS13: PIN_HIGH.6; also elsewhere on the board
DATA_BUS14: PIN_HIGH.7; also elsewhere on the board
DATA_BUS15: PIN_HIGH.8; also elsewhere on the board
GND: SV1.5; also elsewhere on the board
HIGHADDR1: LOW.9; also elsewhere on the board
HIGHADDR2: MID.13; also elsewhere on the board
HIGHADDR3: LOW.11; also elsewhere on the board
HIGHADDR4: MID.15; also elsewhere on the board
HIGHADDR5: LOW.13; also elsewhere on the board
HIGHADDR6: HIGH.1; also elsewhere on the board
HIGHADDR7: LOW.15; also elsewhere on the board
HIGHADDR8: HIGH.3; also elsewhere on the board
HIGHADDR9: MID.1; also elsewhere on the board
HIGHADDR10: HIGH.5; also elsewhere on the board
HIGHADDR11: MID.3; also elsewhere on the board
HIGHADDR12: HIGH.7; also elsewhere on the board
HIGHADDR13: MID.5; also elsewhere on the board
HIGHADDR14: HIGH.9; also elsewhere on the board
HIGHADDR15: MID.7; also elsewhere on the board
ODD_ADDR: SV1.1; also elsewhere on the board
VCC: SV1.2, SV1.3, SV1.6; also elsewhere on the board
